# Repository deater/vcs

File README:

Testing out some VCS programming using the ca65 assembler

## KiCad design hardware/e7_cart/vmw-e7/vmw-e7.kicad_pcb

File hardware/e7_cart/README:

Working on plan to put this on a real E7 cartridge.
Sacrificing a burgertime cart

Bought a bunch.  Singapore is epoxy blob, but made in US
	has through-hole DIP

Of the number I got, only one totally working of DIP type.
	Possibly known they go bad?

Board has E7 mapper, two ROMs (one 8k, one 4k) and
	TMM2009P-25A which is really hard to find, but probably
	1K SRAM (vaguely pin comaptible with 6116)
	But the -A means 1k with the A10 line always high?
	Investigating

Using TL866 to dump roms
	linux minipro tool

	minipro -y -p "2732A @DIP24"  -r 4k_dump.rom

Compare ROMs:
	the 4k rom matches!

Added complication:
	the pinout for the 8k ROMs is the MCM68766 format
	however as far as I can tell this is a somewhat obscure
	non-standard format (24-pin DIP for 8k) and though it is found
	in old machines, like the IBM 5150, you need an adapter to
	a 27C64 DIP28 if you want to read/write to it with regular
	equipment.

	They do sell adapters so I guess I'll try that, though I am worried
	a bit about clearance issues

.  The minipro can't read it

Helpful links:

info on RAM
	https://x.com/RetroWizzard/status/1395835483888967693

SC-3000 basic cartridge also has TMM2009 RAM
	https://www.smspower.org/forums/12958-SC3000BasicLevelIIIABoardPictures

	Undocumented by Toshiba, really hard to find info

	The TMM2009-A (we have) is a 1k SRAM in a 2k SRAM package,
		with A10 tied to 5V?
	The TMM2009-B is the same but ground instead (which is maybe why
		the A10/GND jumper is there

atariage on E7 boards

	https://forums.atariage.com/topic/352717-boards-and-mattel-e7-backswing-options/

	Other boards that use the E7:
	+ Masters of the Universe
	+ Bump 'n Jump

Update: July 2026

+ Made custom new board in Ki-cad (see the vmw-e7 directory)

+ Transferred known good chips from old board (desoldered) to new one:
	works!

+ Used EPROM with same data using adapter sockets: ????

	Have D2764D (64k-bit, 8k-byte) EPROMs

	Burgertime memory layout is 12k across the two chips, one 4k one 8k

	My attempt to rip the 4k ROM only gave the first 2k for some reason?
	My EPROM burner isn't capable of reading the 8K roms

	The prepared ROM dumps are 16k

		It looks like the 4k ROM happens first, doubled
6018 48ad f0f9		0000-07ff (0k-2k) 4k ROM bottom  (6e0-7ff all $00)
0201 0804 f3b6		0800-0fff (2k-4k) data
6018 48ad f0f9		1000-17ff (4k-6k) first 2k repeats?
0201 0804 f3b6		1800-1fff (6k-8k)

0000 0000 0000		2000-27ff (8k-10k)
e8ad a2ff a9fd		2800-2fff (10k-12k) data
0408 0102 0b20		3000-37ff (12k-14k) first 2k repeats?
ffff ffff ffff		3800-3fff (14k-16k) 800-bff = $ff, a00-fff = $00

			0000:1000 (but 6e0-7FF is $00 and 800-fff is $ff)

	split the 16k ROM into two 8k chunks with the "dd" tool

	UPD2764 @DIP28

	minipro -y -p "UPD2764 @DIP28" -w bt_8k.bin

	adapters are 2764-27512 to MCM68766 adapters from
		(originally for use in IBM 5150)
		"go4retro.com" 
	https://minuszerodegrees.net/5150/motherboard/IBM%205150%20motherboard%20-%20Use%20of%202364%20adapter.htm
	https://store.go4retro.com/2364-adapter/

	In the end, it works!

+ Change RAM to 2k version: ????
	https://www.jameco.com/z/HM6116P-3-HITACHI-IC-6116P-3-CMOS-SRAM-16-384-Bit-2Kx8-150ns_42809.html

	Try putting in an HM6116P
		causes glitch?

	should jumper RAM a10 to ground (there was a pin on the original
		PCB to allow this)
	didn't seem to help

+ Try EPROM programmed with Myst!  ???

	dd if=myst.e7 of=myst_rom2.bin bs=1k count=8
	dd if=myst.e7 of=myst_rom1.bin bs=1k count=8 skip=8

	minipro -y -p "UPD2764 @DIP28" -w myst_rom2.bin

Further update
	https://forums.atariage.com/topic/352627-is-this-a-prototype-or-a-bootleg/
	Unreleased AD&D Towers of Mystery board is E7 with 2k of RAM!
	Pictures of the prototype use TC5516AP RAM which has again slightly
		different CS/OE behavior.  Hmmmm.

	https://www.atarimania.com/game-atari-2600-vcs-advanced-dungeons--dragons-tower-of-mystery-cartridge_15999.html
https://www.atariprotos.com/2600/software/towerofmystery/towerofmystery.htm

Here's a bit of info on what is going on in the Myst game.

The title screen / intro loads fine  as it only uses ROM

The linking book at the start runs fine as it only 
	uses some of the 256-byte RAM window for animation
	
main.s:
	sets ROM window to BANK5
	sets small RAM window to BANK0

	displays title (bank6_intro/title.s)
		yes the code is in bank6 dir but actually lives in BANK5

	sets ROM window to BANK6
	runs cleft animation	(bank6_intro/cleft)
	runs book animation (bank6_intro/book)

	book animation uses 256byte RAM window only
		data decompresses from ROM BANK6 to 256-byte RAM bank

	actual gameplay more complicated:
		copies 256 bytes of compresses data from ROM to RAM
		(can't decompress directly from ROM to big-RAM as
		can't be mapped in at same time)
		
		enables RAM into the 1k ROM window

		decompresses 256 bytes of data from small RAM window
			to big RAM window

		the first 16 bytes of the large RAM window copies to 
			zero page

Related work:
	https://xayax.net/bang!/
	Made demo for 32k/128Byte Atari SARA "SuperChip"
	Also made a "real" cart using salvaged SARA chip
	RAM has more limitations than E7

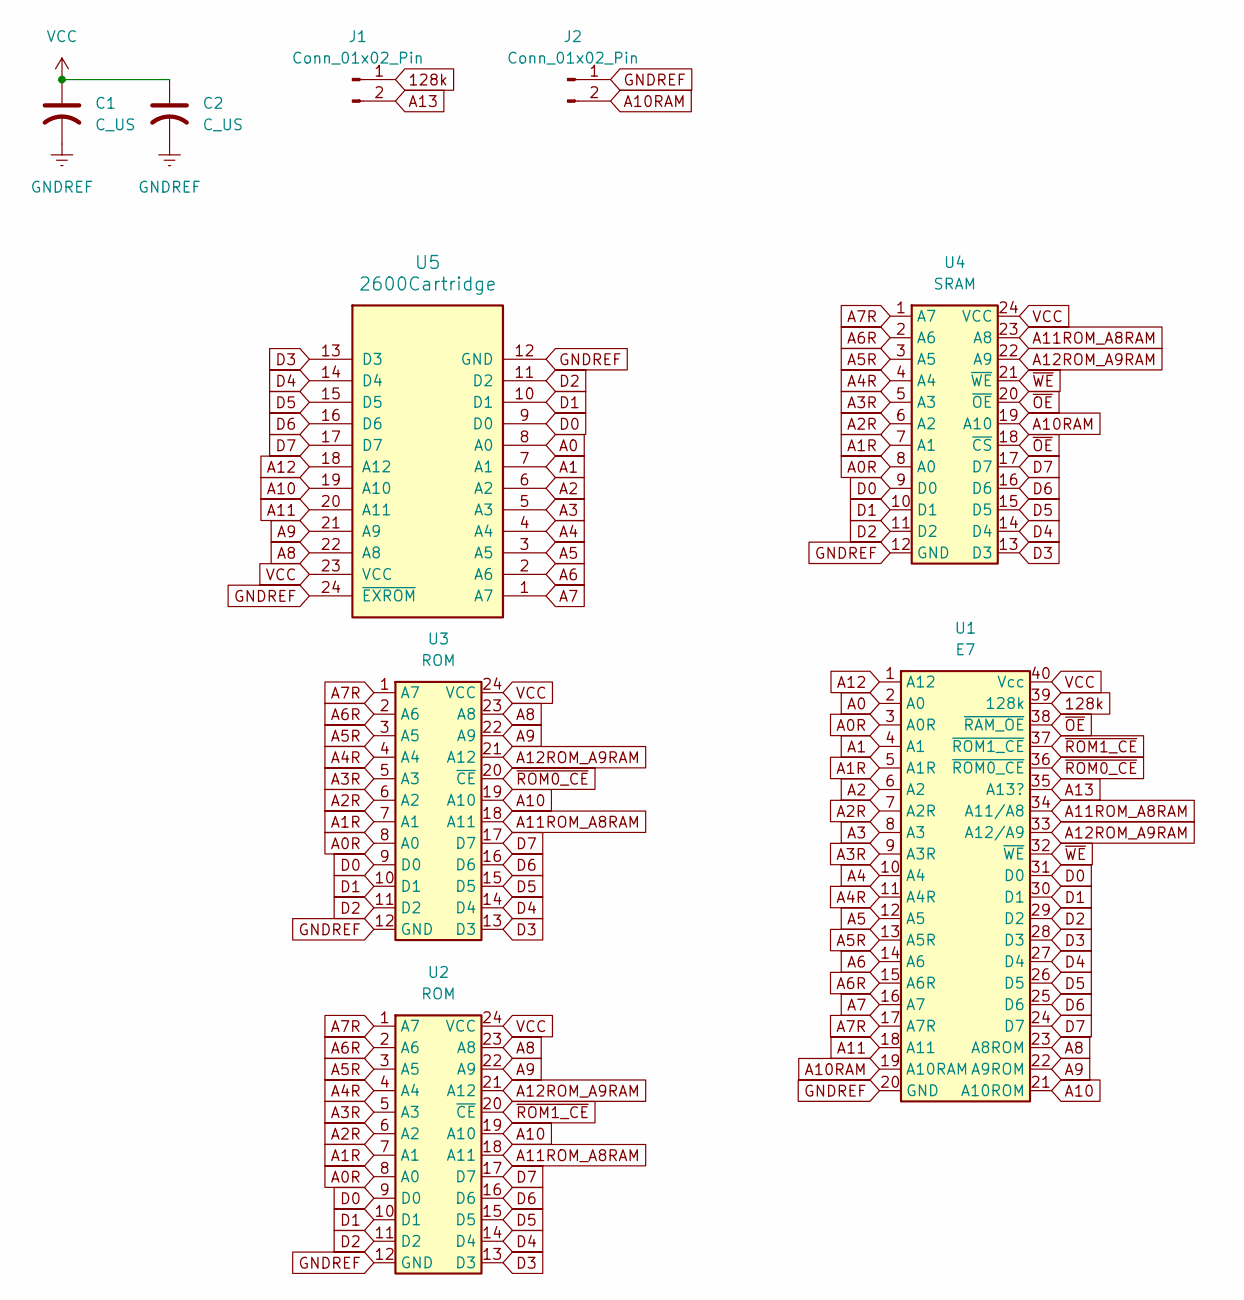
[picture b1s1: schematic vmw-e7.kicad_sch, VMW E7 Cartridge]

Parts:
C1, C2: C_US; C_Disc_D3.0mm_W1.6mm_P2.50mm
J1, J2: Conn_01x02_Pin; PinHeader_1x02_P2.54mm_Vertical
U1: E7; DIP-40_W15.24mm_Socket
U2, U3: ROM; DIP-24_W15.24mm
U4: SRAM; DIP-24_W15.24mm
U5: 2600Cartridge; 2600CART

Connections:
128k: J1.1, U1.39 (128k)
A0: U1.2 (A0), U5.8 (A0)
A0R: U1.3 (A0R), U2.8 (A0), U3.8 (A0), U4.8 (A0)
A1: U1.4 (A1), U5.7 (A1)
A1R: U1.5 (A1R), U2.7 (A1), U3.7 (A1), U4.7 (A1)
A2: U1.6 (A2), U5.6 (A2)
A2R: U1.7 (A2R), U2.6 (A2), U3.6 (A2), U4.6 (A2)
A3: U1.8 (A3), U5.5 (A3)
A3R: U1.9 (A3R), U2.5 (A3), U3.5 (A3), U4.5 (A3)
A4: U1.10 (A4), U5.4 (A4)
A4R: U1.11 (A4R), U2.4 (A4), U3.4 (A4), U4.4 (A4)
A5: U1.12 (A5), U5.3 (A5)
A5R: U1.13 (A5R), U2.3 (A5), U3.3 (A5), U4.3 (A5)
A6: U1.14 (A6), U5.2 (A6)
A6R: U1.15 (A6R), U2.2 (A6), U3.2 (A6), U4.2 (A6)
A7: U1.16 (A7), U5.1 (A7)
A7R: U1.17 (A7R), U2.1 (A7), U3.1 (A7), U4.1 (A7)
A8: U1.23 (A8ROM), U2.23 (A8), U3.23 (A8), U5.22 (A8)
A9: U1.22 (A9ROM), U2.22 (A9), U3.22 (A9), U5.21 (A9)
A10: U1.21 (A10ROM), U2.19 (A10), U3.19 (A10), U5.19 (A10)
A10RAM: J2.2, U1.19 (A10RAM), U4.19 (A10)
A11: U1.18 (A11), U5.20 (A11)
A11ROM_A8RAM: U1.34 (A11/A8), U2.18 (A11), U3.18 (A11), U4.23 (A8)
A12: U1.1 (A12), U5.18 (A12)
A12ROM_A9RAM: U1.33 (A12/A9), U2.21 (A12), U3.21 (A12), U4.22 (A9)
A13: J1.2, U1.35 (A13?)
D0: U1.31 (D0), U2.9 (D0), U3.9 (D0), U4.9 (D0), U5.9 (D0)
D1: U1.30 (D1), U2.10 (D1), U3.10 (D1), U4.10 (D1), U5.10 (D1)
D2: U1.29 (D2), U2.11 (D2), U3.11 (D2), U4.11 (D2), U5.11 (D2)
D3: U1.28 (D3), U2.13 (D3), U3.13 (D3), U4.13 (D3), U5.13 (D3)
D4: U1.27 (D4), U2.14 (D4), U3.14 (D4), U4.14 (D4), U5.14 (D4)
D5: U1.26 (D5), U2.15 (D5), U3.15 (D5), U4.15 (D5), U5.15 (D5)
D6: U1.25 (D6), U2.16 (D6), U3.16 (D6), U4.16 (D6), U5.16 (D6)
D7: U1.24 (D7), U2.17 (D7), U3.17 (D7), U4.17 (D7), U5.17 (D7)
GNDREF: C1.2, C2.2, J2.1, U1.20 (GND), U2.12 (GND), U3.12 (GND), U4.12 (GND), U5.12 (GND), U5.24 (~EXROM)
VCC: C1.1, C2.1, U1.40 (Vcc), U2.24 (VCC), U3.24 (VCC), U4.24 (VCC), U5.23 (VCC)
~OE: U1.38 (~RAM_OE), U4.18 (~CS), U4.20 (~OE)
~ROM0_CE: U1.36 (~ROM0_CE), U3.20 (~CE)
~ROM1_CE: U1.37 (~ROM1_CE), U2.20 (~CE)
~WE: U1.32 (~WE), U4.21 (~WE)

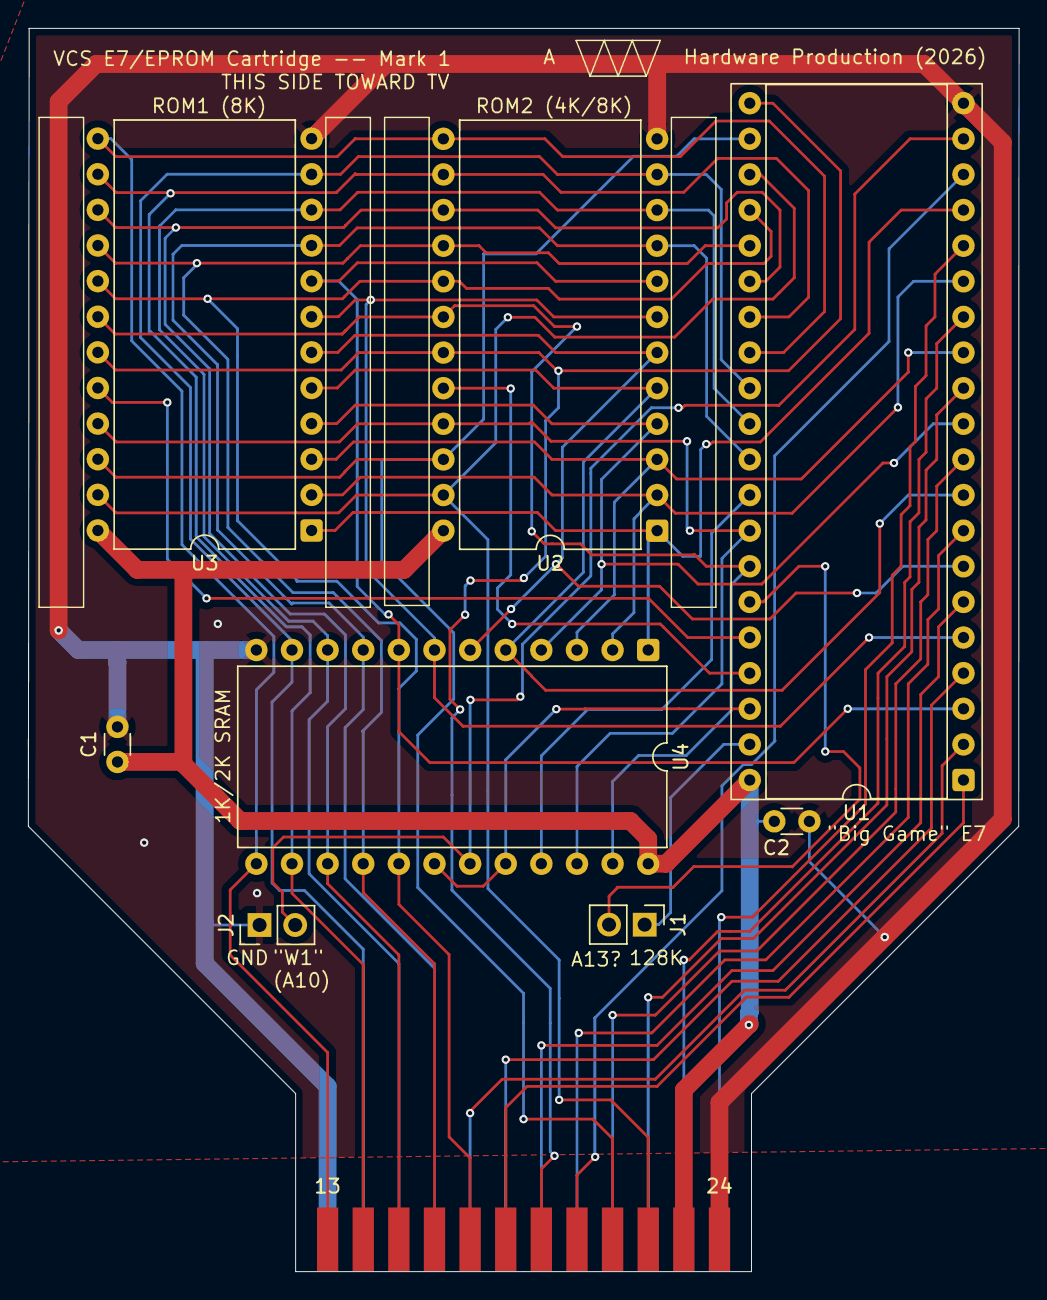
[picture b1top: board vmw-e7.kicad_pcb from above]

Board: 2 copper layers, 70.6 x 88.6 mm, 9 parts (1 on the bottom side), 40 nets.

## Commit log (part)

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2023-06-26 myst: can now pick up the white page
    it's not white yet though
2023-06-26 myst: white page is now actually white
2023-06-27 myst: add another location
    starting to run out of room...
2023-06-27 myst: work more on end sequence
2023-06-28 myst: hook up green book
2023-06-28 myst: add another location
    running out of room
2023-06-28 myst: forgot file
2023-06-28 myst: working on getting more grab actions supported
2023-06-29 myst: re-arrange a lot of stuff to make grabbing easier
2023-06-29 myst: can "win" game and even continue on after
2023-06-29 myst: add last two walls in the library
2023-06-29 myst: add hint from sirrus
2023-06-29 myst: have the door opening play sound effect
    door doesn't actually open
    also glitches, maybe sfx must be page aligned
2023-06-29 myst: turn off debug temporarily so you have to flip all marker switches
2023-07-05 myst: work on fireplace puzzle
2023-07-07 myst: working on fireplace puzzle
2023-07-13 myst: more work on fireplace puzzle
2023-07-13 myst: more work on fireplace puzzle
    all displays right maybe
2023-07-13 myst: more work on fireplace
    can now flip on/off row1
2023-07-14 myst: massively optimize fireplace puzzle
    only re-draw the row we actually touch
2023-07-14 myst: more fireplace work
    work on consistent timing
2023-07-14 myst: constant time on the fireplace puzzle
2023-07-14 myst: fix to have unified sound
    saves a few bytes, was also getting weird bug where depending on where
    you were the sound effects were mapped wrong
2023-07-14 myst: re-arrange things so fits again
    running so low on room
2023-07-14 myst: fix some glitching
    urgh timing
2023-07-15 myst: re-work position code to be more exact
    this actually ends up shrinking the code a bit
2023-07-15 myst: fireplace puzzle more or less working
    completely out of space
    putting off re-doing the sprite positioning stuff
2023-07-17 myst: work on clock puzzle
2023-07-17 myst: update clock test
2023-07-18 myst: sort of have prototype clock going
2023-07-18 myst: optimize clock code
2023-07-18 myst: free up some room so we can try to hook up clock puzzle
    mostly moving sound code to rom6
2023-07-18 myst: can get to clock puzzle now
2023-07-18 myst: move bank5 files into own directory
2023-07-19 myst: fix weird glitch in book cover
    was because there was a RTS at $1EE9 and the CPU glitches
    and sends $1FE9 on the bus causing the RAM page to change
    mid-decompress
    shuffled things around so it doesn't happen, but not a proper fix
2023-07-19 myst: update implementation info on the bug
2023-07-20 myst: add hint screen
2023-07-20 myst: add last two locations
2023-07-20 myst: forgot a file
2023-07-20 myst: optimize the hand update code
    saves some bytes
2023-07-20 myst: optimize hand drawing some more
2023-07-20 myst: update timing comments
2023-07-21 myst: use more centralized position code
2023-07-21 myst: re-arranging the level data
    probably not worth it. saves a few bytes per level
2023-07-21 myst: update graphics offsets
2023-07-21 myst: fix more locations
2023-07-22 myst: shaving some more bytes off bank6
2023-07-22 myst: fix up library
2023-07-22 myst: adjust book spacing
2023-07-23 myst: raising bridge works
    can't see it yet though
2023-07-23 myst: massive re-arrange of things to fit in available space
    freed up some much-needed space in main
2023-07-23 myst: fix title again
    had gone one byte over
2023-07-24 myst: fix library door open/close
    was taking too long and causing a screen glitch
2023-07-24 myst: fix some issues with newer versions of ca65
    can't handle large constants
2023-07-25 myst: working on sizes
2023-07-25 myst: update TODO list
2023-07-25 myst: add some comments
2023-07-25 myst: move lots of stuff around in prep for further work
    probably broke some stuff
2023-07-25 myst: can pick up red/blue pages
    can't really do anything with them though
2023-07-26 myst: more work on red/blue pages
2023-07-26 myst: can have page when looking at book
2023-07-26 myst: working on pages some more
2023-07-27 myst: more work on books
    I know this doesn't actually build, need to move more files to
    another ROM bank
2023-07-27 myst: urgh compiles again
    making a big mess of things
2023-07-27 myst: can put page into red/blue book
2023-07-27 myst: fix some minor issues with locations
2023-07-28 myst: make sure you can't pick up the page again if already in book
2023-07-28 myst: can pick up pages in the fireplace now
2023-07-28 myst: more progress on picking up fireplace pages
2023-07-28 myst: red/blue sorta work as expected in fireplace
    a bit of a hack, rectangular pages
2023-07-28 myst: shave few more bytes off of the title
2023-07-28 myst: shave some bytes off cleft code
2023-07-28 myst: re-arrange the roms to consolidate free space
2023-07-28 myst: unwisely adding two more locations
2023-07-28 myst: more rom rearranging
2023-07-28 myst: more rom rearranging
    managed to free up 512 bytes or so in the end
2023-07-28 myst: more prep for new locations
2023-07-29 myst: working on book overlays
    taking too much space
2023-07-29 myst: update implementation notes
2023-07-30 myst: minor optimization to book code
2023-07-30 myst: optimize cleft a bit
2023-07-30 myst: move title so it doesn't cross page
2023-07-31 myst: work on timing of inside fireplace
    re-use code, but in end only saved 7 bytes
2023-07-31 myst: more work on cycle counting
2023-07-31 myst: change button code to take two scanlines
    probably can't get grab to properly fit in just one
2023-07-31 myst: back to 262 scanlnes for all marker switches
2023-07-31 myst: make the open/close paintings make noise if already open/close
    wasting a lot of bytes on this
2023-07-31 myst: streamline rotation code
2023-07-31 myst: work on glitches on fireplace/clock exit
2023-07-31 myst: fine tune inside elevator
2023-07-31 myst: path to the hint was broken
2023-07-31 myst: work out the page glitch
2023-07-31 myst: update manual
2023-08-01 myst: check pointer bounds so we can't go too far off screen
2023-08-02 myst: comment and reformat the zx02 decompression
    trying to figure out weird delay issue with rocket_close
2023-08-02 myst: check some things off TODO list
2023-08-02 myst: update TODO
2023-08-03 myst: fix "you win" message being half missing
    was a stray extra zero byte in the level definition
2023-08-03 myst: start support for delay when color/bw switch flipped
2023-08-03 myst: update cleft code to shave off a few bytes
    tricky as there are alignment concerns
2023-08-03 myst: work on eliminating glitches
    a lot closer. Still issues with green book
2023-08-03 myst: more progress on keeping 262 scanlines in book
2023-08-03 myst: last known glitch?
2023-08-04 myst: put some info in the "empty" unaccessible 512 byts of the ROM
2023-08-04 myst: hook up inside elevator
    doesn't seem to be room for inside dentist :(
2023-08-04 myst: update the manual
2023-08-04 myst: turn off debugging
    successfully won the game with no glitches in stella
2023-08-06 myst: fix some locations, re-arrange to make some more room
2023-08-06 myst: still making room for things
2023-08-06 myst: unwisely moving things around to allow one more location
2023-08-06 myst: adjust bounds on the paintings
2023-08-07 myst: think I have everything working again
2023-08-07 myst: update docs minorly
2023-08-07 myst: fix embarassing bug when click out of book
2024-08-20 myst: update notes on E7 cartridge
2024-08-21 myst: update rom notes
2024-12-05 sb5: update title screen
2024-12-05 snb5: add snake sprite
2024-12-05 sb5: only draw top half of title
2024-12-06 sb5: split title screen
2024-12-06 sb5: work on two-toned snake
    really want it 3-toned
2024-12-06 sb5: title looking good
2024-12-09 sb5: work on game
2024-12-12 sb5: more work on game
2024-12-29 snake_boxer: more work
2024-12-30 snake_boxer: more work on health bars
2024-12-31 snake_boxer: sorta have sprites working together
2025-01-01 snake_boxer: more progress
2025-01-02 snake boxer: more work on timing
2025-01-03 snake_boxer: update knockouts
2025-01-03 snake_boxer: update numbers a bit
2025-01-03 snake_boxer: initial block support
2025-01-03 snake_boxer: have snake different color based on level
2025-01-03 snake_boxer: track KOs and score KOs separately
    we need it in BCD for score but regular for color
2025-01-03 snake_boxer: count down lives properly
2025-01-06 snake_boxer: update
2025-01-06 snake_boxer: save space with 4-pixel block boxer sprite
2025-01-06 snake_boxer: clean up and comment code
2025-01-06 snake_boxer: update sprites
2025-01-07 snake_boxer: more sprite data
2025-01-07 snake_boxer: add more sprites
2025-01-08 snake_boxer: add running sprites
2025-01-09 snake_boxer: work on intro
2025-01-09 snake_boxer: got 4-color logo going
2025-01-09 snake_boxer: size optimize a bit
2025-01-09 snake_boxer: running animation sort of there
2025-01-10 snake_boxer: have the videlectrix theme playing
2025-01-10 snake_boxer: work on converting to 8k ROM
2025-01-10 snake_boxer: move title screen in with the intro
2025-01-10 snake_boxer: 8k cart all hooked up
2025-01-11 snake_boxer: add RNG
2025-01-11 snake_boxer: snake actually attacks now
2025-01-11 snake_boxer: fix scanlines with snake movement
2025-01-11 snake_boxer: can finally punch
2025-01-11 snake_boxer: blocking works again
2025-01-12 snake_boxer: blink when snake KO
2025-01-12 snake_boxer: more work on hooking up game logic
2025-01-12 snake_boxer: more work on proper game logic
2025-01-13 snake_boxer: start adding collision detection
2025-01-13 snake_boxer: have collision detection more or less working
2025-01-15 snake_boxer: work on convering to 16-bit fixed point
2025-01-16 snake_boxer: make movement use 16-bit fixed point
2025-01-16 snake_boxer: adjust left limit for boxer
2025-01-16 snake_boxer: adjust blocking graphic
2025-01-16 snake_boxer: get harder as goes along
2025-01-21 parallax: get to 262 scanlines
2025-01-21 parallax: size-optimizing
2025-01-21 parallax: optimize
2025-01-22 parallax: optimize more
2025-01-22 parallax: more size optimization
2025-01-24 cometsong: work on music
2025-01-25 parallax: back to stable scanlines
2025-01-25 parallax: optimize some more
2025-01-27 parallax: work on music
2025-01-28 parallax: work on sound
2025-01-28 parallax: force some assumptions on the music
2025-01-28 parallax: hard-code music assumptions
2025-01-29 parallax: under 256, still need a byte
2025-01-29 parallax: finally small enough
2025-01-29 utils: add pad_rom util
    couldn't figure out how to have th cc65 linker do it
2025-01-29 pad_rom: handle mirroring
    note, only works if integer multiple size
2025-01-30 parallax: add TODO
2025-01-30 1k demo: some notes
2025-02-04 tiny: add some example tiny demos
2025-02-04 tiny: get a few more examples compiling
2025-02-04 tiny: working on my own
2025-02-05 tiny: more tiny programs
2025-02-05 tiny demos: move to central place
2025-02-06 cbars: 16b demo
2025-02-10 lb25: move things around
2025-02-10 lb25: clean up some code
2025-02-10 lb25: work on 1k
2025-02-10 tiny: a few more
2025-02-11 lb25: more work on 32b
2025-02-11 bytebeat: add example
2025-02-11 bytebeat: comment code
2025-02-11 bytebeat: work on vsync version
2025-02-11 bytebeat: almost have 262 scanlines going
2025-02-12 bytebeat: continue cycle count
2025-02-12 bytebeat: more work on timing
2025-02-12 bytebeat: some more timing
2025-02-12 bytebeat: update comments
2025-02-12 lb25: purple_beat: fix so works on real hardware
    need to init differently as real hardware+harmony cart starts
    with stack pointer not at $FD
2025-02-12 lb25: fix up parallax to work on real hardware
2025-03-04 snakeboxer: working on music
2025-03-05 snb: more work on music
2025-03-05 lb25: some Makefile updates
2025-03-31 sb5: split the code up between title and gameplay
2025-03-31 sb5: add some code comments
2025-04-01 sb5: forgot Makefile
2025-05-30 move some files around
2026-06-17 e7 board: working on layout
2026-06-17 e7: more work on schematic
2026-06-18 e7: update
2026-06-22 e7: more work on pcb
2026-06-22 e7: pbc mostly done
2026-06-22 e7: clip off some unneeded parts of the board
2026-06-23 e7: add another filter cap, give some more clearance to DIP pins
